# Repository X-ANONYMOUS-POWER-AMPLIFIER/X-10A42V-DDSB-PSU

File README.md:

# X-10A42V-DDSB-PSU - DUAL IN ONE 10A 42V DC SYMMETRICAL PSU FOR POWER AMPLIFIER IN DOUBLE-SIDED CIRCUIT BOARD

X-10A42V-DDSB-PSU is a dual in one PSU circuit module in one double-sided circuit board designed to supply the operating voltage for power amplifier main-circuit module such as [X-B120W-4](https://github.com/X-ANONYMOUS-POWER-AMPLIFIER/X-B120W-4) and/or [X-B120W-4-LITE](https://github.com/X-ANONYMOUS-POWER-AMPLIFIER/X-B120W-4-LITE). It provides split dual 42V DC symmetrical outputs with 10A DC current handling capability applies GBU1006 rectifier diodes, 12V DC non-symmetrical output, and 15V DC symmetrical outputs.

This PSU circuit module provides advanced groundings specialized for power amplifier as: audio grounds, power/PSU grounds, and chassis grounds. It is completed with inrush current limiter applies 7 ohms - 15 Amperes Inrush Current Limiter (NTC Thermistor) type MS32-7R015 product from Vishay / Ametherm. It also completed with AC power entry socket PCB that can be applied for Bulgin AC Power Entry Modules Flange Mount IEC Fused Inlet model PF0002-28.

Note about PCB:
The physical PCB can be split into 4 pieces by cutting on the breakaway-tabs.

## License

1. **License Grant**  
The Licensor hereby grants you a worldwide, royalty-free, non-exclusive, perpetual license to use the circuit design for the non-commercial purposes only.
2. **Conditions**  
Attribution: You must provide credit to the original creator when distributing this circuit design.
3. **Disclaimer of Warranty**  
THE DESIGN IS PROVIDED "AS IS". THE LICENSOR MAKES NO WARRANTIES, EXPRESS OR IMPLIED, REGARDING THE DESIGN, INCLUDING BUT NOT LIMITED TO ANY IMPLIED WARRANTIES OF MERCHANTABILITY OR FITNESS FOR A PARTICULAR PURPOSE.
4. **Limitation of Liability**  
IN NO EVENT SHALL THE LICENSOR BE LIABLE FOR ANY DAMAGES, INCLUDING BUT NOT LIMITED TO DIRECT, INDIRECT, INCIDENTAL, OR CONSEQUENTIAL DAMAGES ARISING OUT OF THE USE OF THE DESIGN.

## Design Files Download

Design files bundle is available for download by follow the URL: [https://github.com/X-ANONYMOUS-POWER-AMPLIFIER/X-10A42V-DDSB-PSU/archive/refs/heads/main.zip](https://github.com/X-ANONYMOUS-POWER-AMPLIFIER/X-10A42V-DDSB-PSU/archive/refs/heads/main.zip)

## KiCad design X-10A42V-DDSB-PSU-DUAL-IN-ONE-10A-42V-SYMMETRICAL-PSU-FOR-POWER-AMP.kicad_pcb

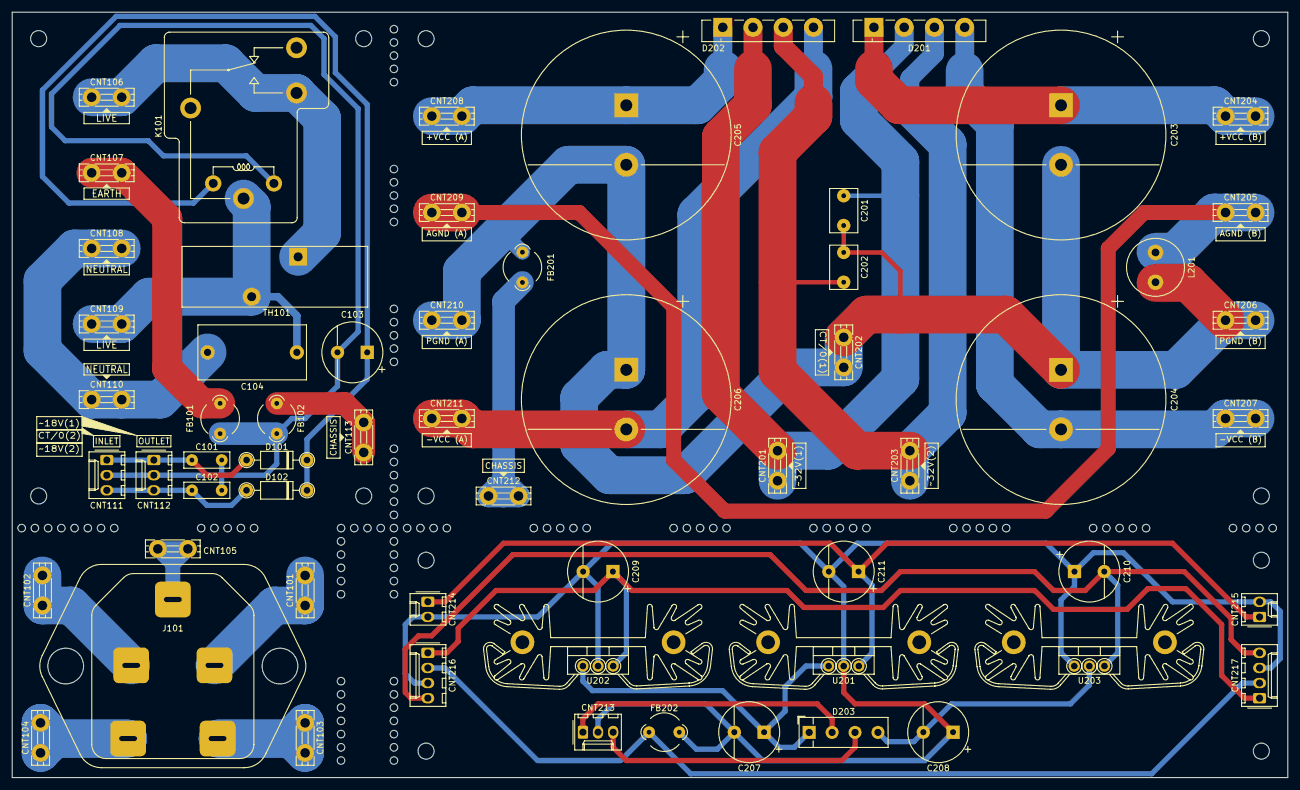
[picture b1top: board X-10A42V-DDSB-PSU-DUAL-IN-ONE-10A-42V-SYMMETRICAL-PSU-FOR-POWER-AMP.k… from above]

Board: 2 copper layers, 214.3 x 128.6 mm, 61 parts (1 on the bottom side), 32 nets.

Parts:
C101, C102: 0.1uF; C_Rect_L7.5mm_W2.5mm_P5.00mm_WIMA_MKS2
C103, C207, C208, C209, C210, C211: 470uF; CP_Radial_D10.0mm_P5.00mm
C104: 0.1uF; C_Rect_L18.0mm_W9.0mm_P15.00mm_FKS3_FKP3
C201, C202: 0.1uF; C_Rect_L7.2mm_W4.5mm_P5.00mm_FKS2_FKP2_MKS2_MKP2
C203, C204, C205, C206: 10000uF; CP_Radial_D35.0mm_P10.00mm_3pin_SnapIn_Chemi-Con
CNT101, CNT102, CNT103, CNT104, CNT105, CNT106, CNT107, CNT108, CNT109, CNT110, CNT113, CNT201, CNT202, CNT203, CNT204, CNT205, CNT206, CNT207, CNT208, CNT209, CNT210, CNT211, CNT212: 2376582-2; PCB_TAB_250_FASTON_TPBR
CNT111, CNT112, CNT213: 22-27-2031; Molex_KK-254_AE-6410-03A_1x03_P2.54mm_Vertical
CNT214, CNT215: 22-27-2021; Molex_KK-254_AE-6410-02A_1x02_P2.54mm_Vertical
CNT216, CNT217: 22-27-2041; Molex_KK-254_AE-6410-04A_1x04_P2.54mm_Vertical
D101, D102: 1N4002; D_DO-41_SOD81_P10.16mm_Horizontal
D201, D202: GBU1006; Diode_Bridge_Vishay_GBU
D203: VS-2KBP005; Diode_Bridge_Vishay_KBPM
FB101, FB102, FB201, FB202: Ferrite Bead; LairdTech_28C0236-0JW-10
J101: PF0002-28; BULGIN-IEC-Connector-PF0002-28
K101: SLA-24VDC-SL-A; Relay_SPDT_RAYEX-L90
L201: Bourns RLB0913-1R0K; L_Radial_D9.5mm_P5.00mm_Fastron_07HVP
TH101: MS32-7R015; NTC_MS32_7R015
U201: L7812CV; TO-220-3_Vertical_Heatsink-SK-104_38.1mm
U202: L7815CV; TO-220-3_Vertical_Heatsink-SK-104_38.1mm
U203: L7915CV; TO-220-3_Vertical_Heatsink-SK-104_38.1mm

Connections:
AGND: CNT205.1, CNT209.1, L201.2
AGND2: CNT216.2, CNT217.2, FB202.1
EGND: C101.2, C102.1, C103.2, CNT111.2, CNT112.2, FB101.2, FB102.2, K101.A2
unnamed: CNT101.1, J101.L
unnamed: CNT102.1, J101.N
unnamed: CNT103.1, J101.F1
unnamed: CNT104.1, J101.F2
unnamed: CNT105.1, J101.E
unnamed: CNT106.1, K101.14, TH101.1
unnamed: CNT107.1, FB101.1
unnamed: C104.2, CNT108.1, CNT110.1
unnamed: C104.1, CNT109.1, K101.11A, TH101.2
unnamed: C101.1, CNT111.1, CNT112.1, D101.2 (A)
unnamed: C102.2, CNT111.3, CNT112.3, D102.2 (A)
unnamed: CNT113.1, FB102.1
unnamed: C201.1, CNT201.1, D201.2, D202.2
unnamed: C202.2, CNT203.1, D201.3, D202.3
unnamed: C203.1, CNT204.1, D201.1 (+)
unnamed: C204.2, CNT207.1, D201.4 (-)
unnamed: C205.1, CNT208.1, D202.1 (+)
unnamed: C206.2, CNT211.1, D202.4 (-)
unnamed: CNT212.1, FB201.1
unnamed: CNT213.1, D203.2
unnamed: CNT213.3, D203.3
unnamed: C211.1, CNT214.1, CNT215.1, U201.3 (V_{O})
unnamed: C209.1, CNT216.1, CNT217.1, U202.3 (V_{O})
unnamed: C210.2, CNT216.4, CNT217.4, U203.3 (V_{O})
unnamed: C103.1, D101.1 (K), D102.1 (K), K101.A1
unnamed: C207.1, D203.1 (+), U201.1 (V_{IN}), U202.1 (V_{IN})
unnamed: C208.2, D203.4 (-), U203.2 (V_{IN})
PGND: C201.2, C202.1, C203.2, C204.1, C205.2, C206.1, CNT202.1, CNT206.1, CNT210.1, FB201.2, L201.1
PGND2: C207.2, C208.1, C209.2, C210.1, C211.2, CNT213.2, CNT214.2, CNT215.2, CNT216.3, CNT217.3, FB202.2, U201.2 (G), U202.2 (G), U203.1 (G)
